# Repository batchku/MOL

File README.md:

# MOL

DEPRECIATED.

Please see:
https://github.com/batchku/MO

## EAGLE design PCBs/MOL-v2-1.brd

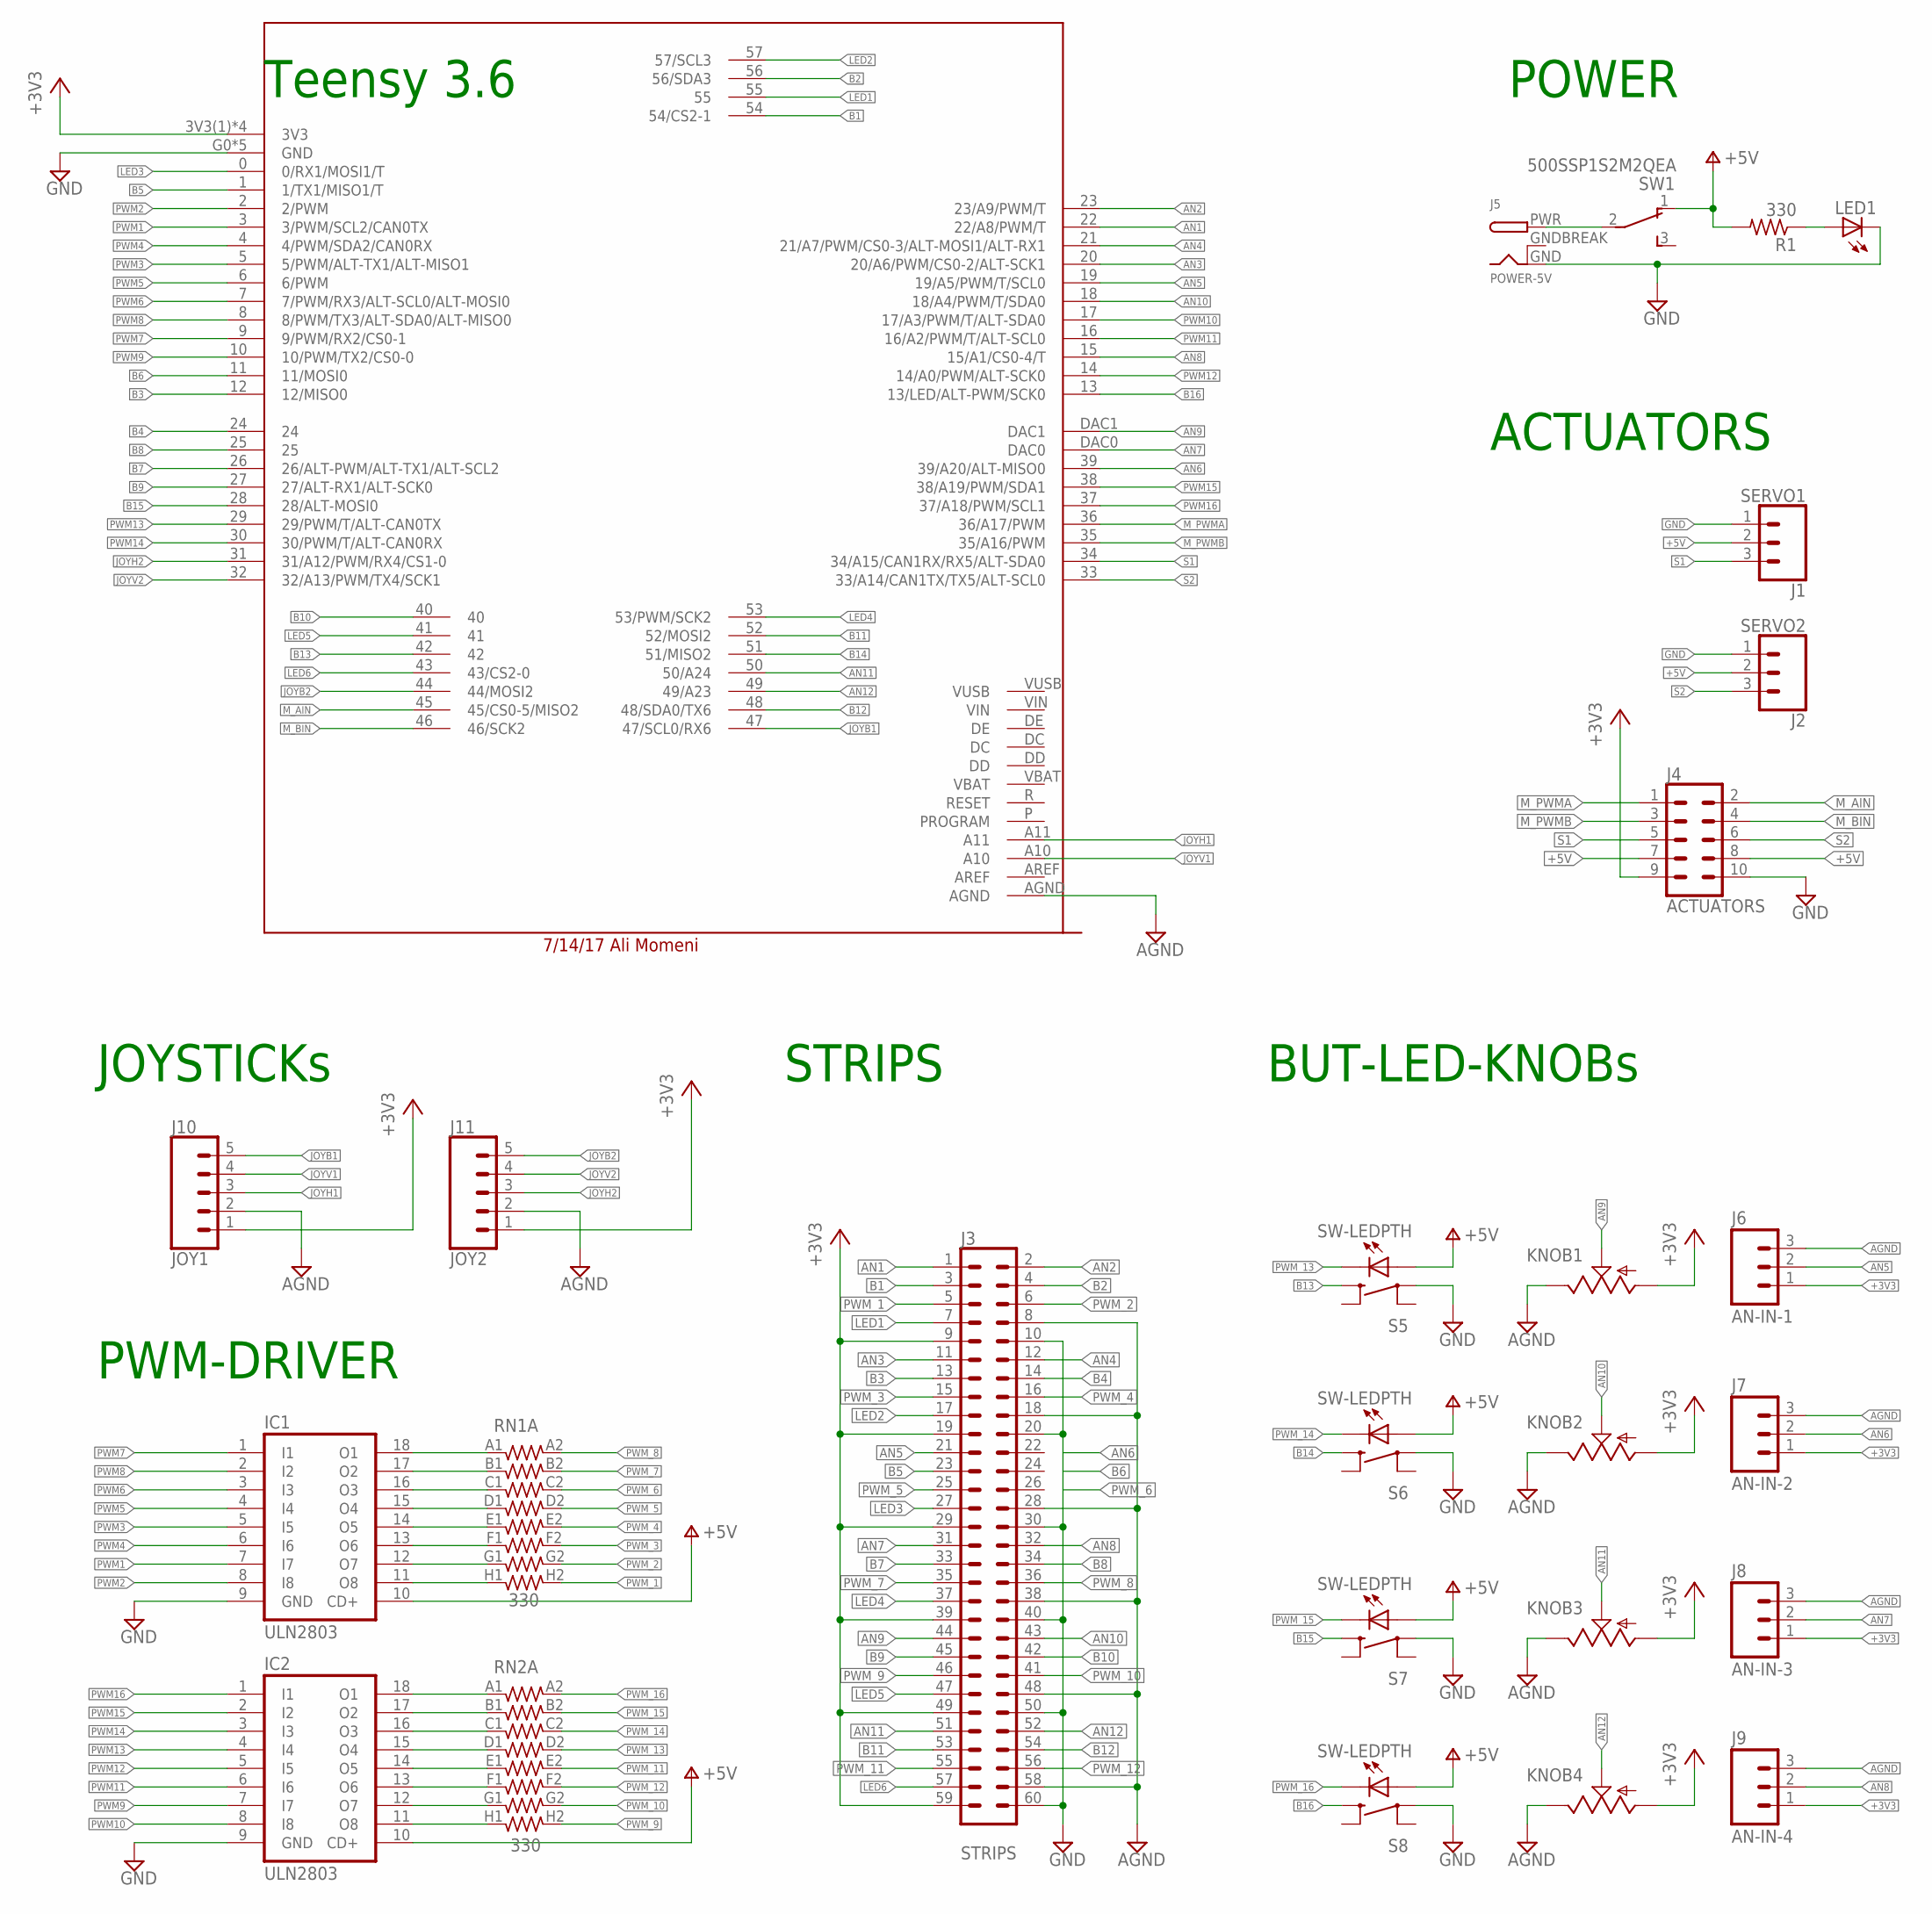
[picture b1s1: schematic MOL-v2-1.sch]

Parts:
IC1, IC2: ULN2803; DIL18
J1: SERVO1; 1X03_LOCK@1
J2: SERVO2; 1X03_LOCK@1
J3: STRIPS; 2X30_SHROUDED
J4: ACTUATORS; 2X5-SHROUDED_LOCK
J5: POWER-5V; DCJACK_2MM_PTH
J6: AN-IN-1; 1X03_NO_SILK
J7: AN-IN-2; 1X03_NO_SILK
J8: AN-IN-3; 1X03_NO_SILK
J9: AN-IN-4; 1X03_NO_SILK
J10: JOY1; 1X05_LOCK
J11: JOY2; 1X05_LOCK
KNOB1, KNOB2, KNOB3, KNOB4: TRIM; TRIM-PCB-9MM
LED1: LED3MM
R1: 330; 0204/7
RN1, RN2: 330; RESISTOR-NET-8P-DIL16
S5, S6, S7, S8: SW-LEDPTH; TR2-SWITCH-MOMENTARY-LED
SW1: 500SSP1S2M2QEA; SWITCH_SPDT_500SSP1S2M2QEA
U$1: TEENSY3_6-ALI_NO-USB-HOST; TEENSY3-6_NO-USB-HOST

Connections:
+3V3: J3.9, J3.19, J3.29, J3.39, J3.49, J3.59, J4.9, J6.1, J7.1, J8.1, J9.1, J10.1, J11.1, KNOB1.1 (A), KNOB2.1 (A), KNOB3.1 (A), KNOB4.1 (A), U$1.3V3(1) (3V3), U$1.3V3(2) (3V3), U$1.3V3(3) (3V3), U$1.3V3(4) (3V3)
+5V: IC1.10 (CD+), IC2.10 (CD+), J1.2, J2.2, J4.7, J4.8, R1.2, SW1.1
AGND: J3.8, J3.18, J3.28, J3.38, J3.48, J3.58, J6.3, J7.3, J8.3, J9.3, J10.2, J11.2, KNOB1.3 (E), KNOB2.3 (E), KNOB3.3 (E), KNOB4.3 (E), U$1.AGND
AN1: J3.1, U$1.22 (22/A8/PWM/T)
AN2: J3.2, U$1.23 (23/A9/PWM/T)
AN3: J3.11, U$1.20 (20/A6/PWM/CS0-2/ALT-SCK1)
AN4: J3.12, U$1.21 (21/A7/PWM/CS0-3/ALT-MOSI1/ALT-RX1)
AN5: J3.21, J6.2, U$1.19 (19/A5/PWM/T/SCL0)
AN6: J7.2, U$1.39 (39/A20/ALT-MISO0)
AN7: J3.31, J8.2, U$1.DAC0
AN8: J3.32, J9.2, U$1.15 (15/A1/CS0-4/T)
AN9: J3.44, KNOB1.2 (S), U$1.DAC1
AN10: J3.43, KNOB2.2 (S), U$1.18 (18/A4/PWM/T/SDA0)
AN11: J3.51, KNOB3.2 (S), U$1.50 (50/A24)
AN12: J3.52, KNOB4.2 (S), U$1.49 (49/A23)
B1: J3.3, U$1.54 (54/CS2-1)
B2: J3.4, U$1.56 (56/SDA3)
B3: J3.13, U$1.12 (12/MISO0)
B4: J3.14, U$1.24
B5: J3.23, U$1.1 (1/TX1/MISO1/T)
B6: U$1.11 (11/MOSI0)
B7: J3.33, U$1.26 (26/ALT-PWM/ALT-TX1/ALT-SCL2)
B8: J3.34, U$1.25
B9: J3.45, U$1.27 (27/ALT-RX1/ALT-SCK0)
B10: J3.42, U$1.40
B11: J3.53, U$1.52 (52/MOSI2)
B12: J3.54, U$1.48 (48/SDA0/TX6)
B13: S5.1, U$1.42
B14: S6.1, U$1.51 (51/MISO2)
B15: S7.1, U$1.28 (28/ALT-MOSI0)
B16: S8.1, U$1.13 (13/LED/ALT-PWM/SCK0)
GND: IC1.9 (GND), IC2.9 (GND), J1.1, J2.1, J3.10, J3.20, J3.30, J3.40, J3.50, J3.60, J4.10, J5.GND, LED1.K (C), S5.3, S6.3, S7.3, S8.3, U$1.G0 (GND), U$1.G1 (GND), U$1.G2 (GND), U$1.G3 (GND), U$1.G6 (GND)
GNDBREAK: J5.GNDBREAK
JOYB1: J10.5, U$1.47 (47/SCL0/RX6)
JOYB2: J11.5, U$1.44 (44/MOSI2)
JOYH1: J10.3, U$1.A11
JOYH2: J11.3, U$1.31 (31/A12/PWM/RX4/CS1-0)
JOYV1: J10.4, U$1.A10
JOYV2: J11.4, U$1.32 (32/A13/PWM/TX4/SCK1)
LED1: J3.7, U$1.55
LED2: J3.17, U$1.57 (57/SCL3)
LED3: J3.27, U$1.0 (0/RX1/MOSI1/T)
LED4: J3.37, U$1.53 (53/PWM/SCK2)
LED5: J3.47, U$1.41
LED6: J3.57, U$1.43 (43/CS2-0)
M_AIN: J4.2, U$1.45 (45/CS0-5/MISO2)
M_BIN: J4.4, U$1.46 (46/SCK2)
M_PWMA: J4.1, U$1.36 (36/A17/PWM)
M_PWMB: J4.3, U$1.35 (35/A16/PWM)
unnamed: J5.PWR, SW1.2
unnamed: LED1.A, R1.1
unnamed: IC1.18 (O1), RN1.A1 (1)
unnamed: IC1.17 (O2), RN1.B1 (1)
unnamed: IC1.16 (O3), RN1.C1 (1)
unnamed: IC1.15 (O4), RN1.D1 (1)
unnamed: IC1.14 (O5), RN1.E1 (1)
unnamed: IC1.13 (O6), RN1.F1 (1)
unnamed: IC1.12 (O7), RN1.G1 (1)
unnamed: IC1.11 (O8), RN1.H1 (1)
unnamed: IC2.18 (O1), RN2.A1 (1)
unnamed: IC2.17 (O2), RN2.B1 (1)
unnamed: IC2.16 (O3), RN2.C1 (1)
unnamed: IC2.15 (O4), RN2.D1 (1)
unnamed: IC2.14 (O5), RN2.E1 (1)
unnamed: IC2.12 (O7), RN2.G1 (1)
unnamed: IC2.11 (O8), RN2.H1 (1)
unnamed: IC2.13 (O6), RN2.F1 (1)
PWM1: IC1.7 (I7), U$1.3 (3/PWM/SCL2/CAN0TX)
PWM2: IC1.8 (I8), U$1.2 (2/PWM)
PWM3: IC1.5 (I5), U$1.5 (5/PWM/ALT-TX1/ALT-MISO1)
PWM4: IC1.6 (I6), U$1.4 (4/PWM/SDA2/CAN0RX)
PWM5: IC1.4 (I4), U$1.6 (6/PWM)
PWM6: IC1.3 (I3), U$1.7 (7/PWM/RX3/ALT-SCL0/ALT-MOSI0)
PWM7: IC1.1 (I1), U$1.9 (9/PWM/RX2/CS0-1)
PWM8: IC1.2 (I2), U$1.8 (8/PWM/TX3/ALT-SDA0/ALT-MISO0)
PWM9: IC2.7 (I7), U$1.10 (10/PWM/TX2/CS0-0)
PWM10: IC2.8 (I8), U$1.17 (17/A3/PWM/T/ALT-SDA0)
PWM11: IC2.6 (I6), U$1.16 (16/A2/PWM/T/ALT-SCL0)
PWM12: IC2.5 (I5), U$1.14 (14/A0/PWM/ALT-SCK0)
PWM13: IC2.4 (I4), U$1.29 (29/PWM/T/ALT-CAN0TX)
PWM14: IC2.3 (I3), U$1.30 (30/PWM/T/ALT-CAN0RX)
PWM15: IC2.2 (I2), U$1.38 (38/A19/PWM/SDA1)
PWM16: IC2.1 (I1), U$1.37 (37/A18/PWM/SCL1)
PWM_1: J3.5, RN1.H2 (2)
PWM_2: J3.6, RN1.G2 (2)
PWM_3: J3.15, RN1.F2 (2)
PWM_4: J3.16, RN1.E2 (2)
PWM_5: J3.25, RN1.D2 (2)
PWM_6: RN1.C2 (2)
PWM_7: J3.35, RN1.B2 (2)
PWM_8: J3.36, RN1.A2 (2)
PWM_9: J3.46, RN2.H2 (2)
PWM_10: J3.41, RN2.G2 (2)
PWM_11: J3.55, RN2.E2 (2)
PWM_12: J3.56, RN2.F2 (2)
PWM_13: RN2.D2 (2), S5.C
PWM_14: RN2.C2 (2), S6.C
PWM_15: RN2.B2 (2), S7.C
PWM_16: RN2.A2 (2), S8.C
S1: J1.3, J4.5, U$1.34 (34/A15/CAN1RX/RX5/ALT-SDA0)
S2: J2.3, J4.6, U$1.33 (33/A14/CAN1TX/TX5/ALT-SCL0)
V+: S5.A, S6.A, S7.A, S8.A

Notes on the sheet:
BUT-LED-KNOBs
JOYSTICKs
PWM-DRIVER
STRIPS
ACTUATORS
POWER
Teensy 3.6

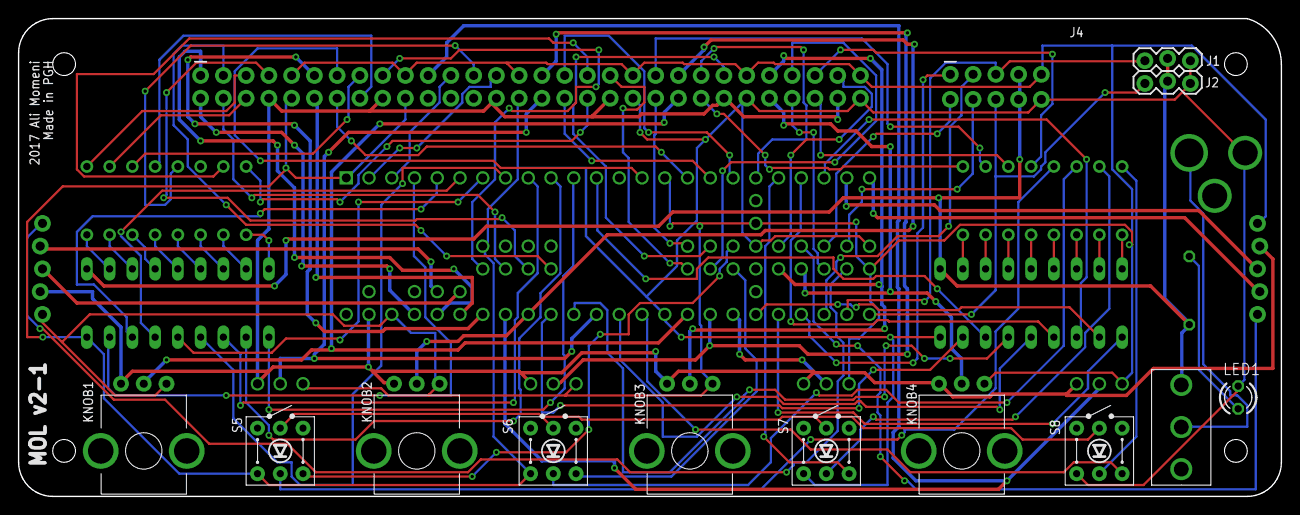
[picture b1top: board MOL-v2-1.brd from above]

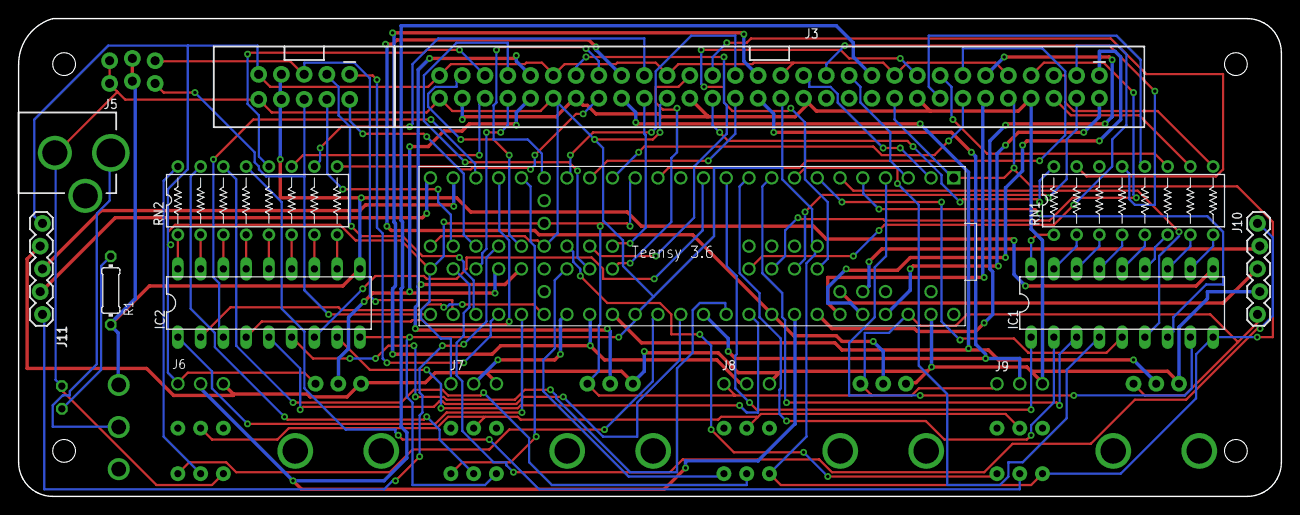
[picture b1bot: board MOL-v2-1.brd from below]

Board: 2 copper layers, 141.0 x 53.3 mm, 27 parts (15 on the bottom side), 99 nets.

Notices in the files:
parts and their libraries:
74LV: Copyright (C) 2008, Bob Starr
SparkFun-Connectors: Licensing: Creative Commons ShareAlike 4.0 International - https://creativecommons.org/licenses/by-sa/4.0
